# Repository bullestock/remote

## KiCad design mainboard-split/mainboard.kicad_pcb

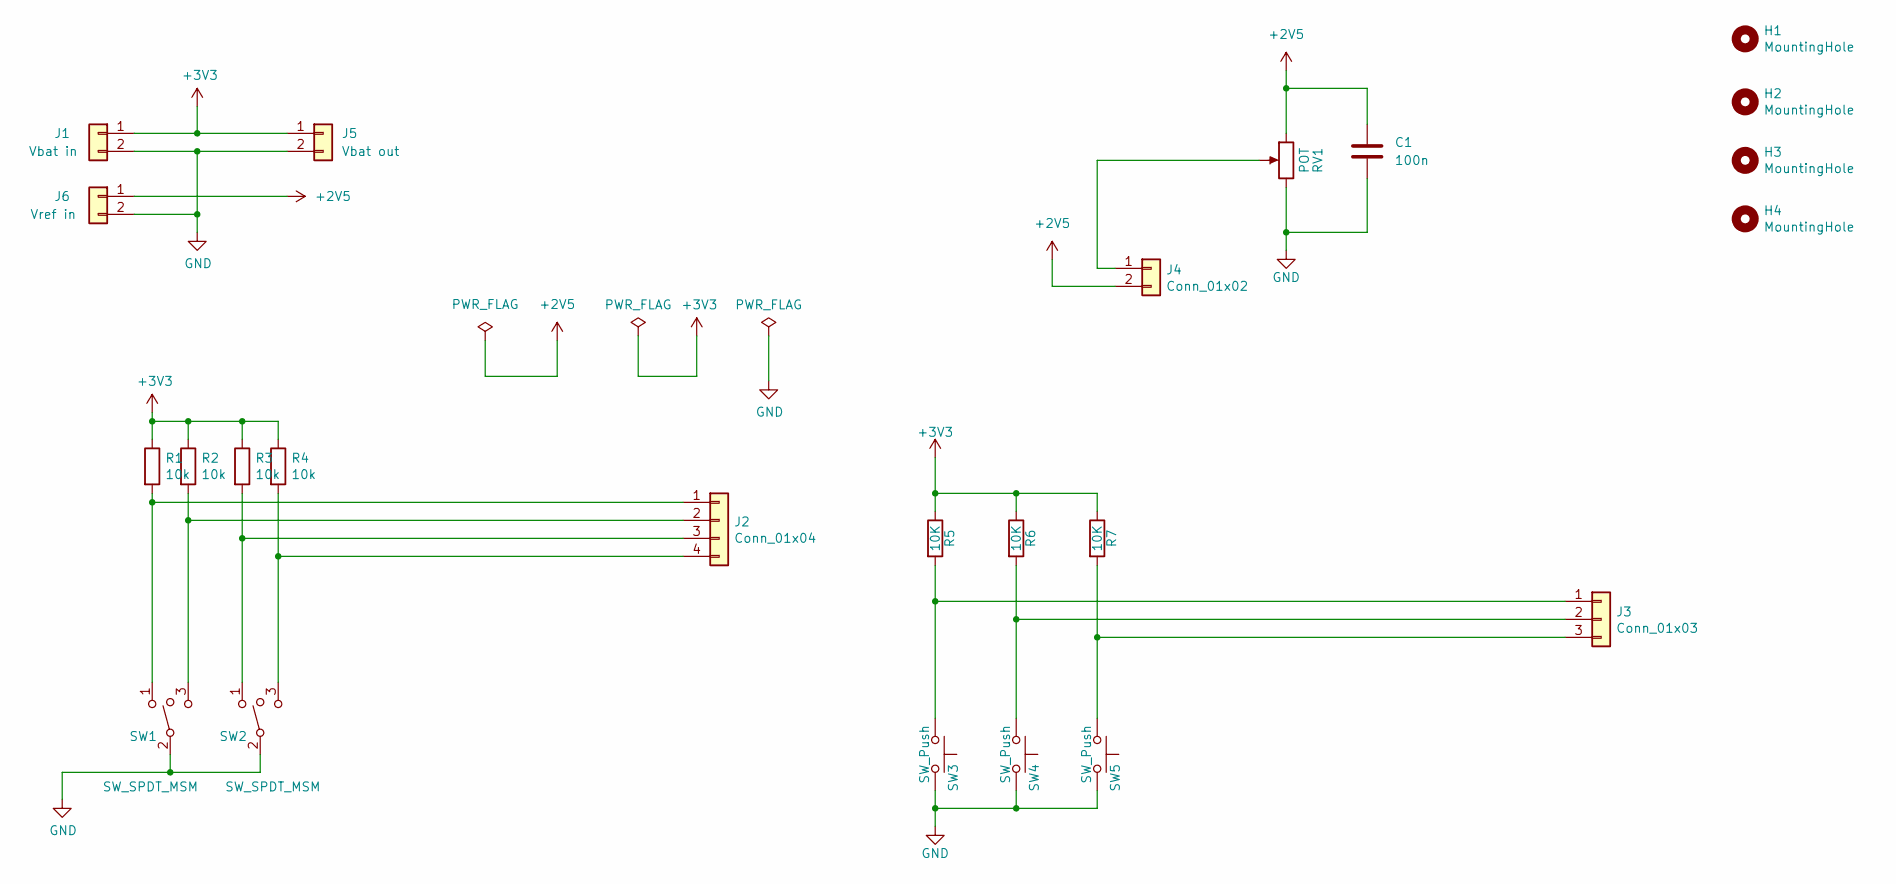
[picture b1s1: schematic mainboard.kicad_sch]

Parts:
C1: 100n; C_0603_1608Metric
H1, H2, H3, H4: MountingHole; MountingHole_3.2mm_M3
J1: Vbat in; JST_XH_B02B-XH-A_1x02_P2.50mm_Vertical
J2: Conn_01x04; JST_XH_B04B-XH-A_1x04_P2.50mm_Vertical
J3: Conn_01x03; JST_XH_B03B-XH-A_1x03_P2.50mm_Vertical
J4: Conn_01x02; JST_XH_B02B-XH-A_1x02_P2.50mm_Vertical
J5: Vbat out; JST_XH_B02B-XH-A_1x02_P2.50mm_Vertical
J6: Vref in; JST_XH_B02B-XH-A_1x02_P2.50mm_Vertical
R1, R2, R3, R4: 10k; R_0603_1608Metric
R5, R6, R7: 10K; R_0603_1608Metric
RV1: POT; Potentiometer_6mm_axis_square
SW1, SW2: SW_SPDT_MSM; Switch_1x03_P5.08mm
SW3, SW4, SW5: SW_Push; Switch_1x02_P6mm

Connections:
+2V5: C1.1, J4.2, J6.1, RV1.1
+3V3: J1.1, J5.1, R1.1, R2.1, R3.1, R4.1, R5.1, R6.1, R7.1
GND: C1.2, J1.2, J5.2, J6.2, RV1.3, SW1.2, SW2.2, SW3.2, SW4.2, SW5.2
unnamed: J2.1, R1.2, SW1.1
unnamed: J2.2, R2.2, SW1.3
unnamed: J2.3, R3.2, SW2.1
unnamed: J2.4, R4.2, SW2.3
unnamed: J3.1, R5.2, SW3.1
unnamed: J3.2, R6.2, SW4.1
unnamed: J3.3, R7.2, SW5.1
unnamed: J4.1, RV1.2

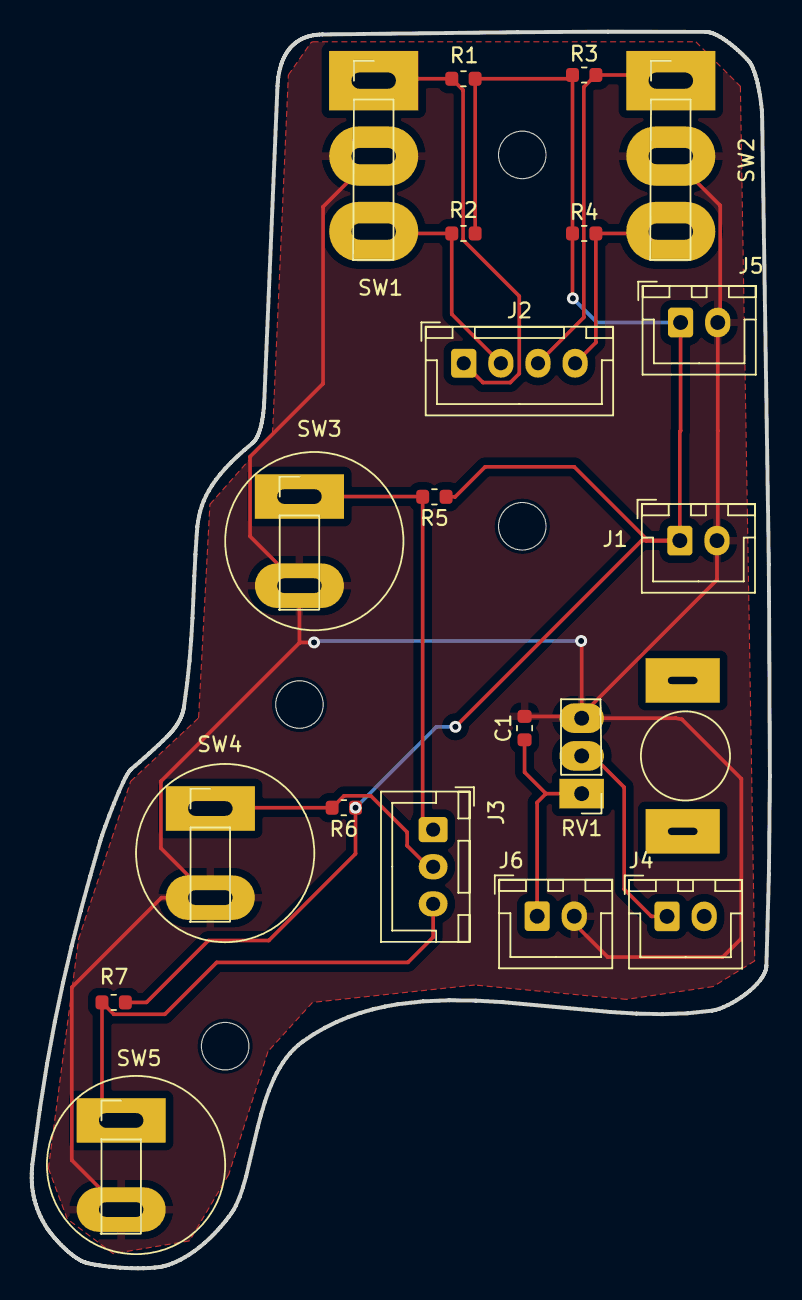
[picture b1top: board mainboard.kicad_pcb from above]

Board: 2 copper layers, 49.7 x 83.3 mm, 24 parts (0 on the bottom side), 11 nets.

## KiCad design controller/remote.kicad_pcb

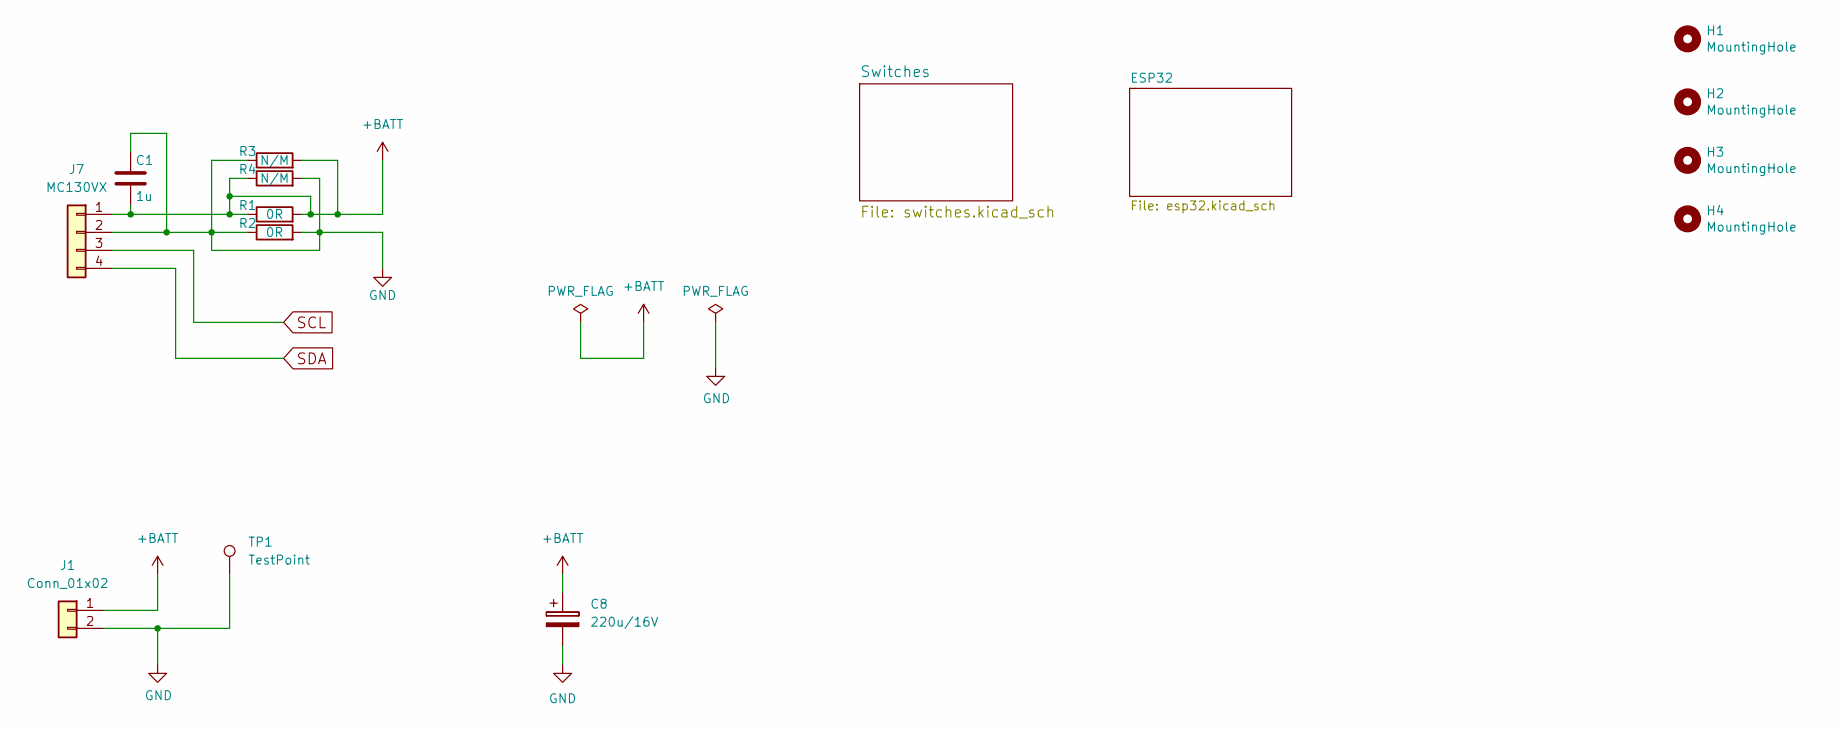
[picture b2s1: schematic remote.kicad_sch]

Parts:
C1: 1u; C_0603_1608Metric
C8: 220u/16V; CP_Elec_10x10.5
H1, H2, H3, H4: MountingHole; MountingHole_3.2mm_M3
J1: Conn_01x02; JST_XH_B02B-XH-A_1x02_P2.50mm_Vertical
J7: MC130VX; PinSocket_1x04_P2.54mm_Vertical
R1, R2: 0R; R_0603_1608Metric
R3, R4: N/M; R_0603_1608Metric
TP1: TestPoint; TestPoint_Keystone_5000-5004_Miniature

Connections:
+BATT: C1.2, C8.1, J1.1, J7.1, R1.1, R1.2, R3.2, R4.1; also elsewhere on the board
GND: C1.1, C8.2, J1.2, J7.2, R2.1, R2.2, R3.1, R4.2, TP1.1; also elsewhere on the board
SCL: J7.3; also elsewhere on the board
SDA: J7.4; also elsewhere on the board

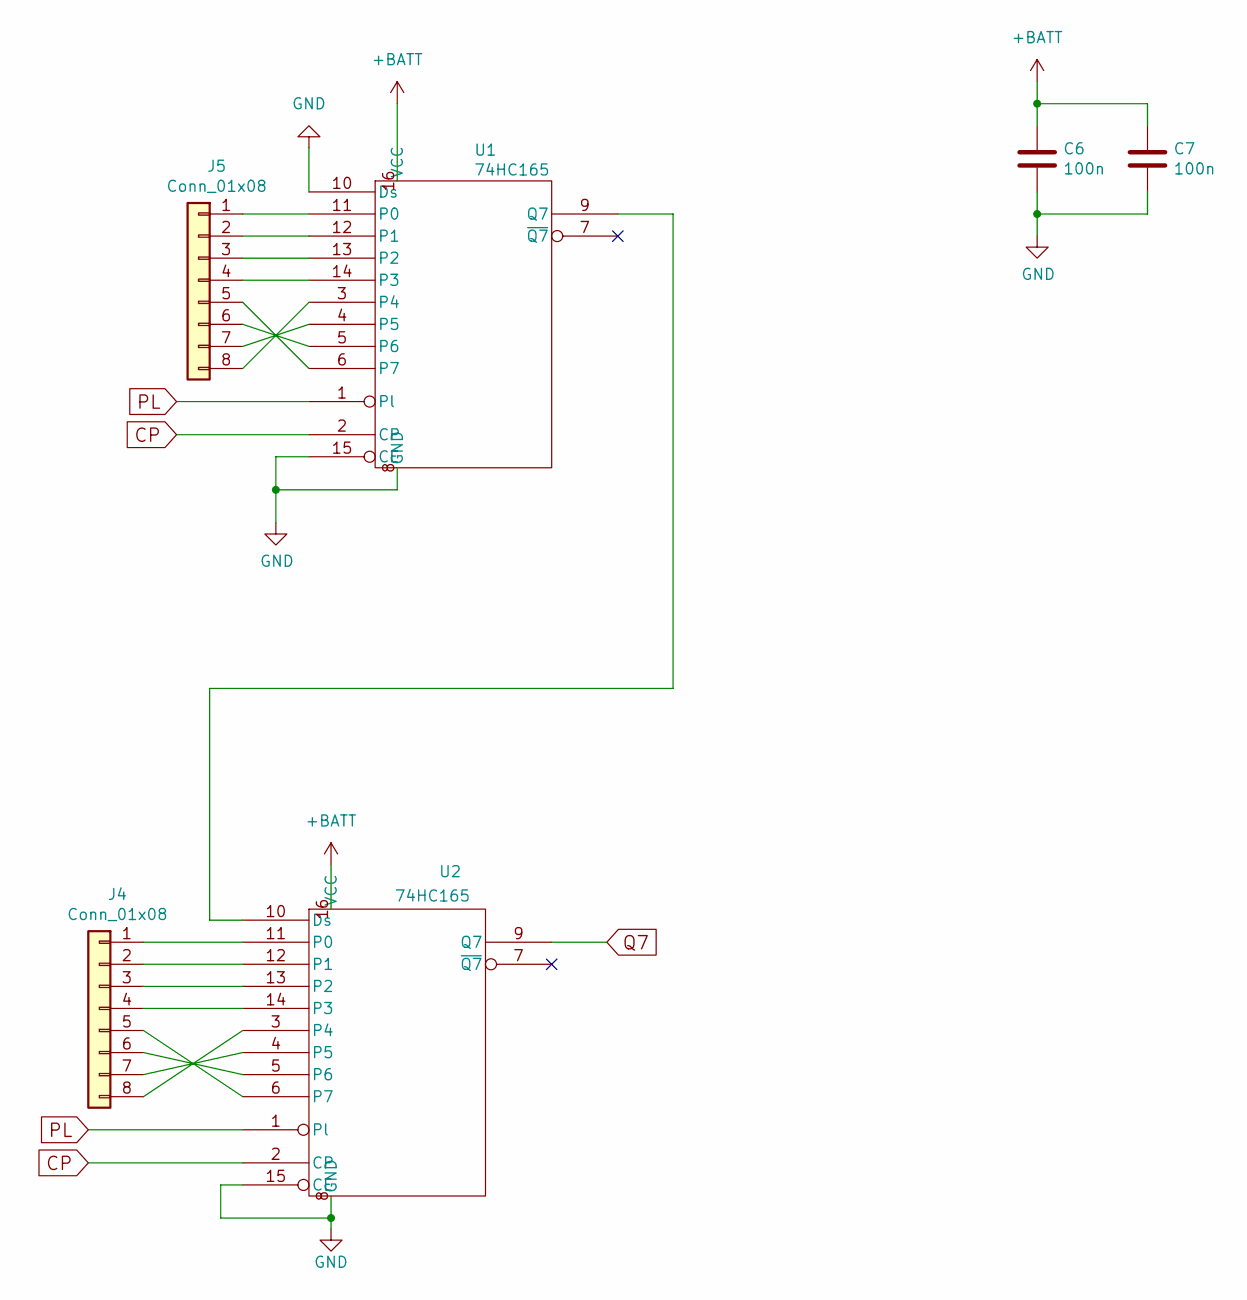
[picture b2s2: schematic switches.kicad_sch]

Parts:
C6, C7: 100n; C_0603_1608Metric
J4, J5: Conn_01x08; JST_XH_B08B-XH-A_1x08_P2.50mm_Vertical
U1, U2: 74HC165; SOP-16_3.9x9.9mm_P1.27mm

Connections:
+BATT: C6.1, C7.1, U1.16 (VCC), U2.16 (VCC); also elsewhere on the board
CP: U1.2 (CP), U2.2 (CP); also elsewhere on the board
GND: C6.2, C7.2, U1.8 (GND), U1.10 (Ds), U1.15 (CE), U2.8 (GND), U2.15 (CE); also elsewhere on the board
unnamed: J4.1, U2.11 (P0)
unnamed: J4.2, U2.12 (P1)
unnamed: J4.3, U2.13 (P2)
unnamed: J4.4, U2.14 (P3)
unnamed: J4.5, U2.6 (P7)
unnamed: J4.6, U2.5 (P6)
unnamed: J4.7, U2.4 (P5)
unnamed: J4.8, U2.3 (P4)
unnamed: J5.1, U1.11 (P0)
unnamed: J5.2, U1.12 (P1)
unnamed: J5.3, U1.13 (P2)
unnamed: J5.4, U1.14 (P3)
unnamed: J5.5, U1.6 (P7)
unnamed: J5.6, U1.5 (P6)
unnamed: J5.7, U1.4 (P5)
unnamed: J5.8, U1.3 (P4)
unnamed: U1.9 (Q7), U2.10 (Ds)
PL: U1.1 (Pl), U2.1 (Pl); also elsewhere on the board
Q7: U2.9 (Q7); also elsewhere on the board

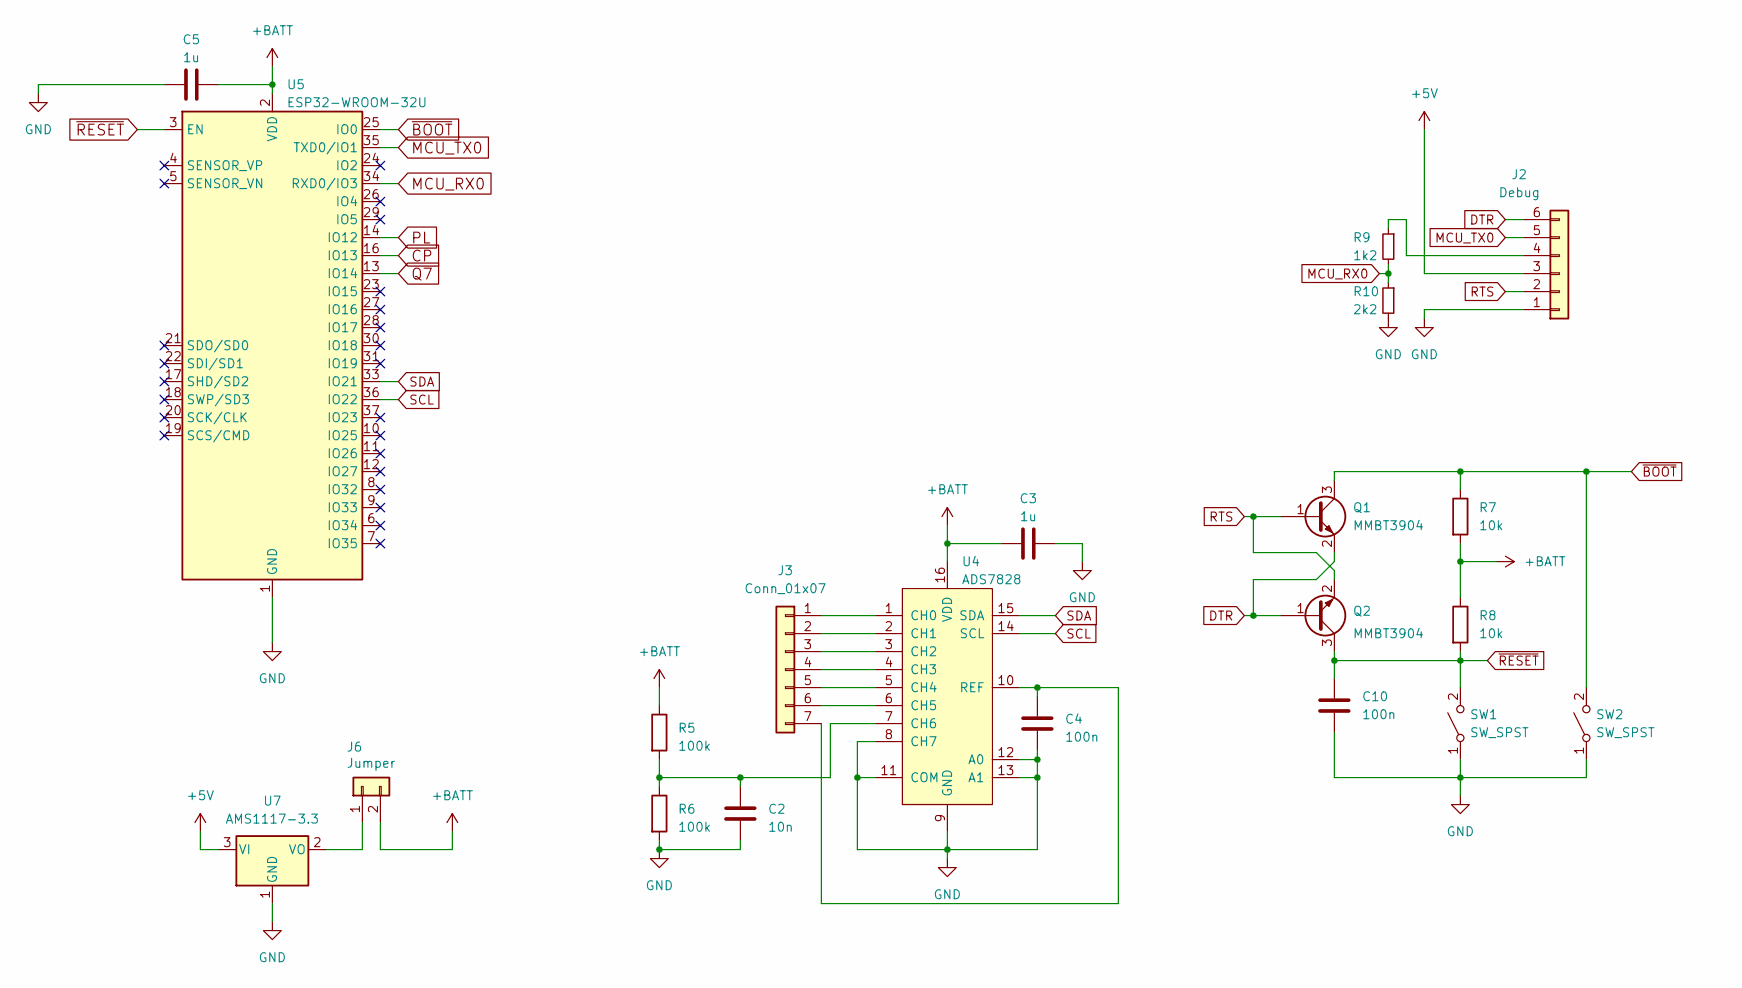
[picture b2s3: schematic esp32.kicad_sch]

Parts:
C2: 10n; C_0603_1608Metric
C3, C5: 1u; C_0603_1608Metric
C4, C10: 100n; C_0603_1608Metric
J2: Debug; PinHeader_1x06_P2.54mm_Vertical
J3: Conn_01x07; JST_XH_B07B-XH-A_1x07_P2.50mm_Vertical
J6: Jumper; PinHeader_1x02_P2.54mm_Vertical
Q1, Q2: MMBT3904; SOT-23
R5, R6: 100k; R_0603_1608Metric
R7, R8: 10k; R_0603_1608Metric
R9: 1k2; R_0603_1608Metric
R10: 2k2; R_0603_1608Metric
SW1, SW2: SW_SPST; SW_SPST_CK_RS282G05A3
U4: ADS7828; TSSOP-16_4.4x5mm_P0.65mm
U5: ESP32-WROOM-32U
U7: AMS1117-3.3; SOT-223-3_TabPin2

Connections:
+5V: J2.3, U7.3 (VI)
+BATT: C3.1, C5.2, J6.2, R5.1, R7.2, R8.1, U4.16 (VDD), U5.2 (VDD); also elsewhere on the board
CP: U5.16 (IO13); also elsewhere on the board
DTR: J2.6, Q1.2 (E), Q2.1 (B)
GND: C2.2, C3.2, C4.2, C5.1, C10.2, J2.1, R6.2, R10.2, SW1.1 (A), SW2.1 (A), U4.8 (CH7), U4.9 (GND), U4.11 (COM), U4.12 (A0), U4.13 (A1), U5.1 (GND), U5.15 (GND), U5.38 (GND), U5.39 (GND), U7.1 (GND); also elsewhere on the board
MCU_RX0: R9.2, R10.1, U5.34 (RXD0/IO3)
MCU_TX0: J2.5, U5.35 (TXD0/IO1)
unnamed: J2.4, R9.1
unnamed: J3.1, U4.1 (CH0)
unnamed: J3.2, U4.2 (CH1)
unnamed: J3.3, U4.3 (CH2)
unnamed: J3.4, U4.4 (CH3)
unnamed: J3.5, U4.5 (CH4)
unnamed: J3.6, U4.6 (CH5)
unnamed: C4.1, J3.7, U4.10 (REF)
unnamed: J6.1, U7.2 (VO)
unnamed: C2.1, R5.2, R6.1, U4.7 (CH6)
PL: U5.14 (IO12); also elsewhere on the board
Q7: U5.13 (IO14); also elsewhere on the board
RTS: J2.2, Q1.1 (B), Q2.2 (E)
SCL: U4.14 (SCL), U5.36 (IO22); also elsewhere on the board
SDA: U4.15 (SDA), U5.33 (IO21); also elsewhere on the board
~BOOT: Q1.3 (C), R7.1, SW2.2 (B), U5.25 (IO0)
~RESET: C10.1, Q2.3 (C), R8.2, SW1.2 (B), U5.3 (EN)

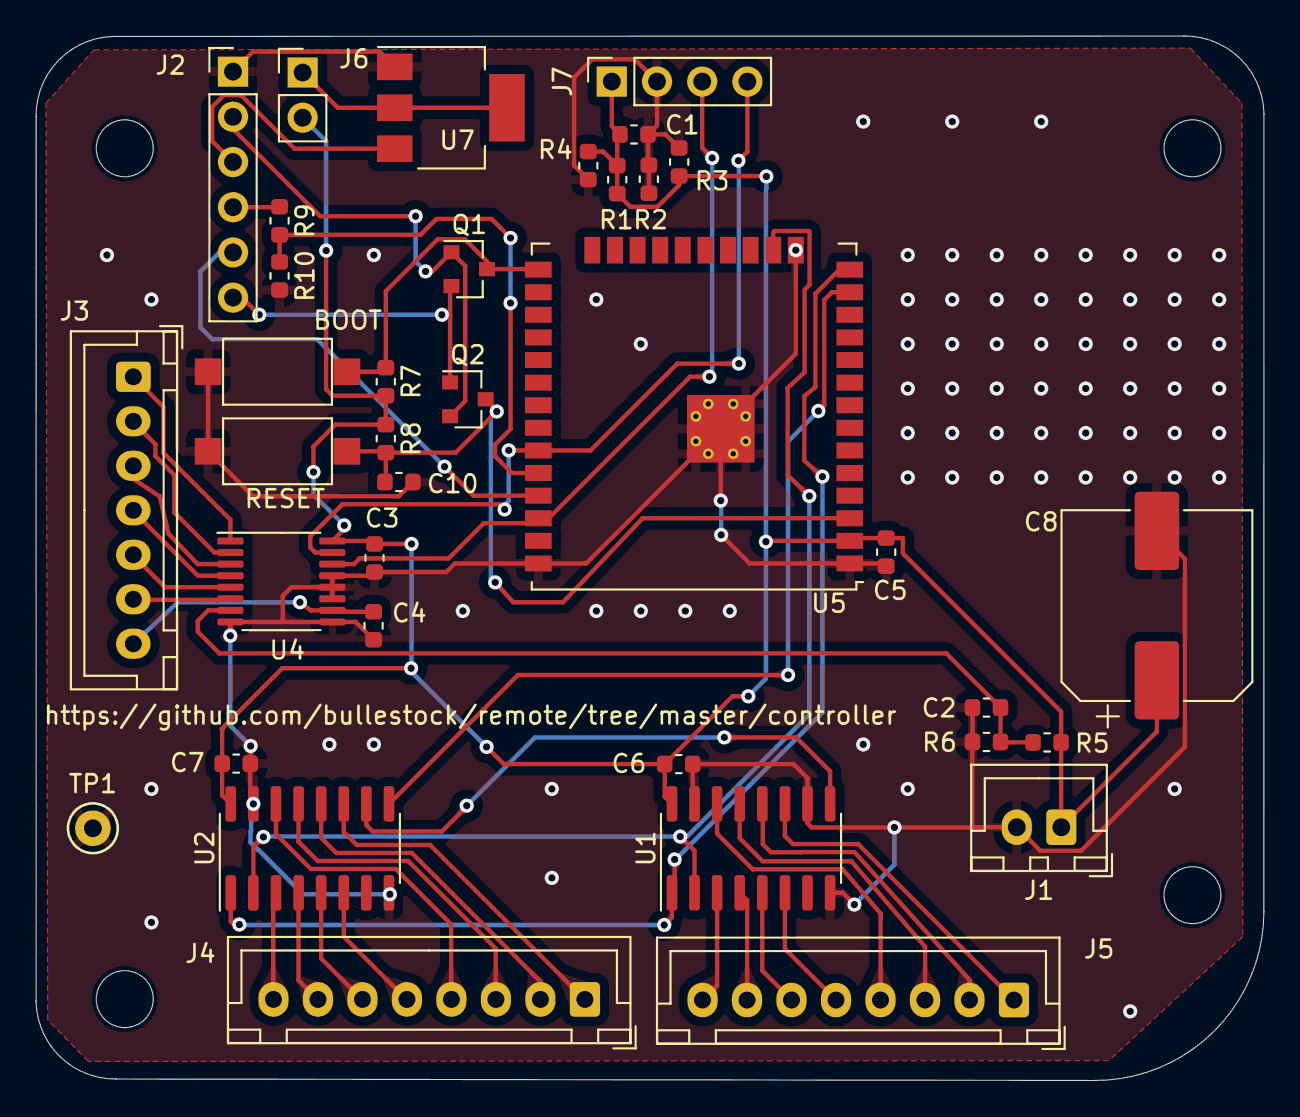
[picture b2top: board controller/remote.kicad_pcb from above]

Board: 2 copper layers, 69.0 x 58.7 mm, 40 parts (0 on the bottom side), 41 nets.

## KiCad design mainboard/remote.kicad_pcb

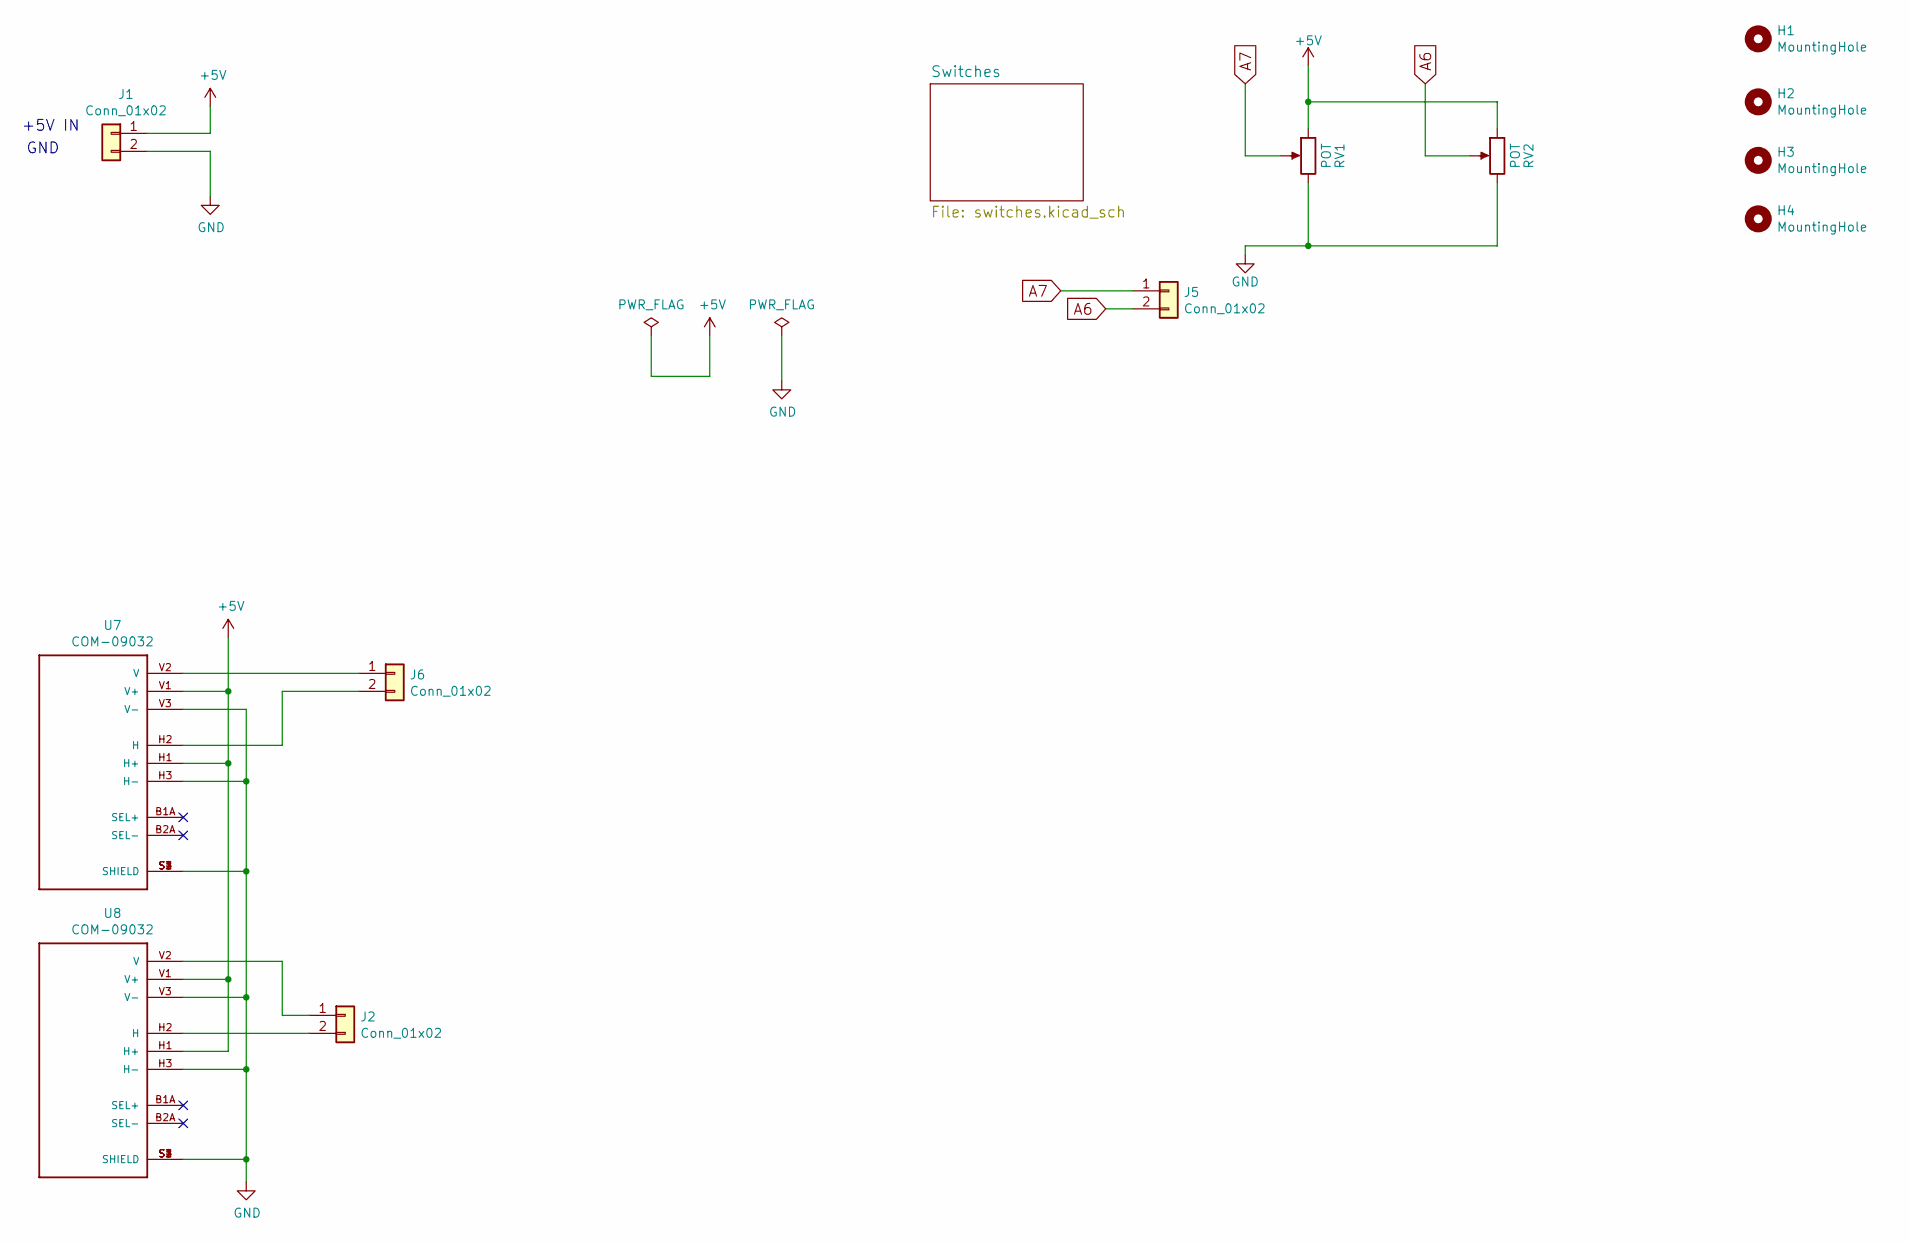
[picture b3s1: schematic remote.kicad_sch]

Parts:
H1, H2, H3, H4: MountingHole; MountingHole_3.2mm_M3
J1, J2, J5, J6: Conn_01x02; JST_XH_B02B-XH-A_1x02_P2.50mm_Vertical_Milling
RV1, RV2: POT; Potentiometer_6mm_axis_square
U7, U8: COM-09032; AnalogJoystick_ALPS_10k

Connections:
+5V: J1.1, RV1.1, RV2.1, U7.H1 (H+), U7.V1 (V+), U8.H1 (H+), U8.V1 (V+); also elsewhere on the board
A6: J5.2, RV2.2
A7: J5.1, RV1.2
GND: J1.2, RV1.3, RV2.3, U7.H3 (H-), U7.S1 (SHIELD), U7.S2 (SHIELD), U7.S3 (SHIELD), U7.S4 (SHIELD), U7.V3 (V-), U8.H3 (H-), U8.S1 (SHIELD), U8.S2 (SHIELD), U8.S3 (SHIELD), U8.S4 (SHIELD), U8.V3 (V-); also elsewhere on the board
unnamed: J2.1, U8.V2 (V)
unnamed: J2.2, U8.H2 (H)
unnamed: J6.1, U7.V2 (V)
unnamed: J6.2, U7.H2 (H)

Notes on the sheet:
GND
+5V IN

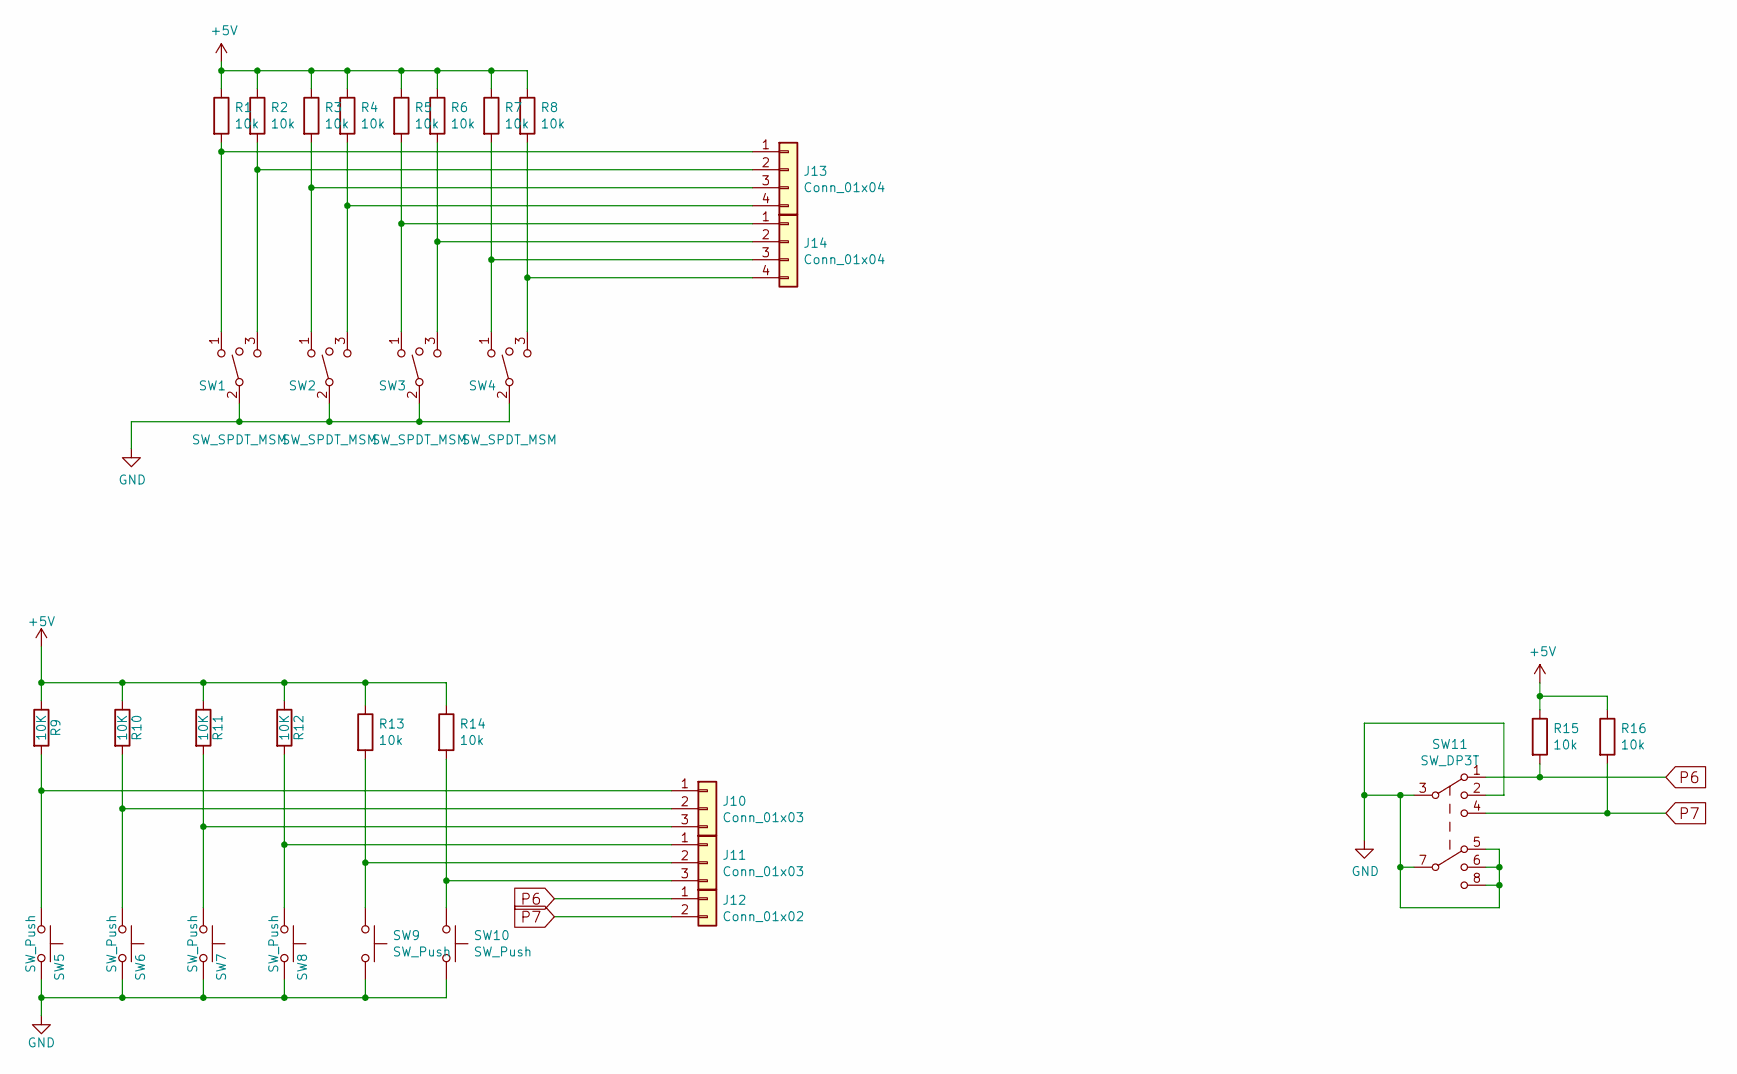
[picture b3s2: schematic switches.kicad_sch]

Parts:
J10, J11: Conn_01x03; JST_XH_B03B-XH-A_1x03_P2.50mm_Vertical_Milling
J12: Conn_01x02; JST_XH_B02B-XH-A_1x02_P2.50mm_Vertical_Milling
J13, J14: Conn_01x04; JST_XH_B04B-XH-A_1x04_P2.50mm_Vertical_Milling
R1, R2, R3, R4, R5, R6, R7, R8, R13, R14, R15, R16: 10k; R_0805_2012Metric
R9, R10, R11, R12: 10K; R_0805_2012Metric
SW1, SW2, SW3, SW4: SW_SPDT_MSM; Switch_1x03_P5.08mm
SW5, SW6, SW7, SW8, SW9, SW10: SW_Push; Switch_1x02_P6mm
SW11: SW_DP3T; Switch_2x03_P3mm_Slide

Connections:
+5V: R1.1, R2.1, R3.1, R4.1, R5.1, R6.1, R7.1, R8.1, R9.1, R10.1, R11.1, R12.1, R13.1, R14.1, R15.1, R16.1; also elsewhere on the board
GND: SW1.2, SW2.2, SW3.2, SW4.2, SW5.2, SW6.2, SW7.2, SW8.2, SW9.2, SW10.2, SW11.2, SW11.3, SW11.5, SW11.6, SW11.7, SW11.8; also elsewhere on the board
unnamed: J10.1, R9.2, SW5.1
unnamed: J10.2, R10.2, SW6.1
unnamed: J10.3, R11.2, SW7.1
unnamed: J11.1, R12.2, SW8.1
unnamed: J11.2, R13.2, SW9.1
unnamed: J11.3, R14.2, SW10.1
unnamed: J13.1, R1.2, SW1.1
unnamed: J13.2, R2.2, SW1.3
unnamed: J13.3, R3.2, SW2.1
unnamed: J13.4, R4.2, SW2.3
unnamed: J14.1, R5.2, SW3.1
unnamed: J14.2, R6.2, SW3.3
unnamed: J14.3, R7.2, SW4.1
unnamed: J14.4, R8.2, SW4.3
P6: J12.1, R15.2, SW11.1
P7: J12.2, R16.2, SW11.4

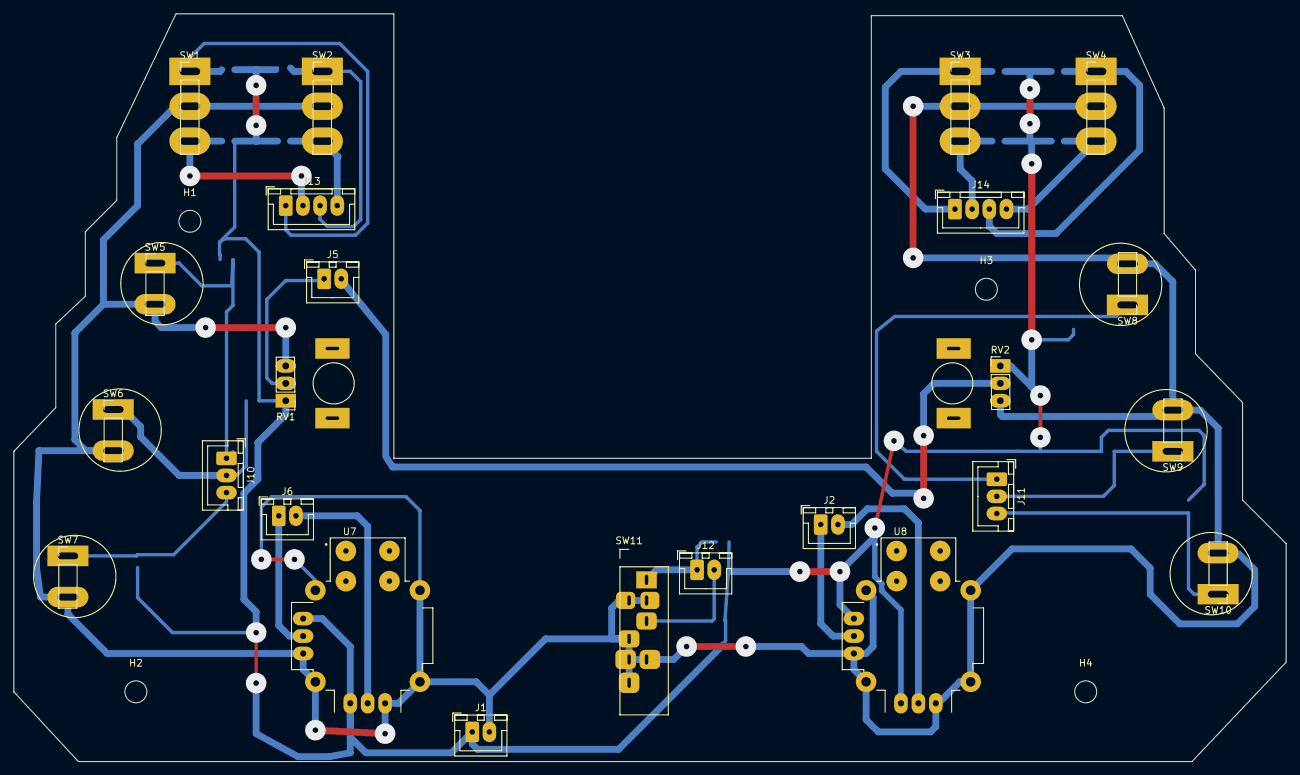
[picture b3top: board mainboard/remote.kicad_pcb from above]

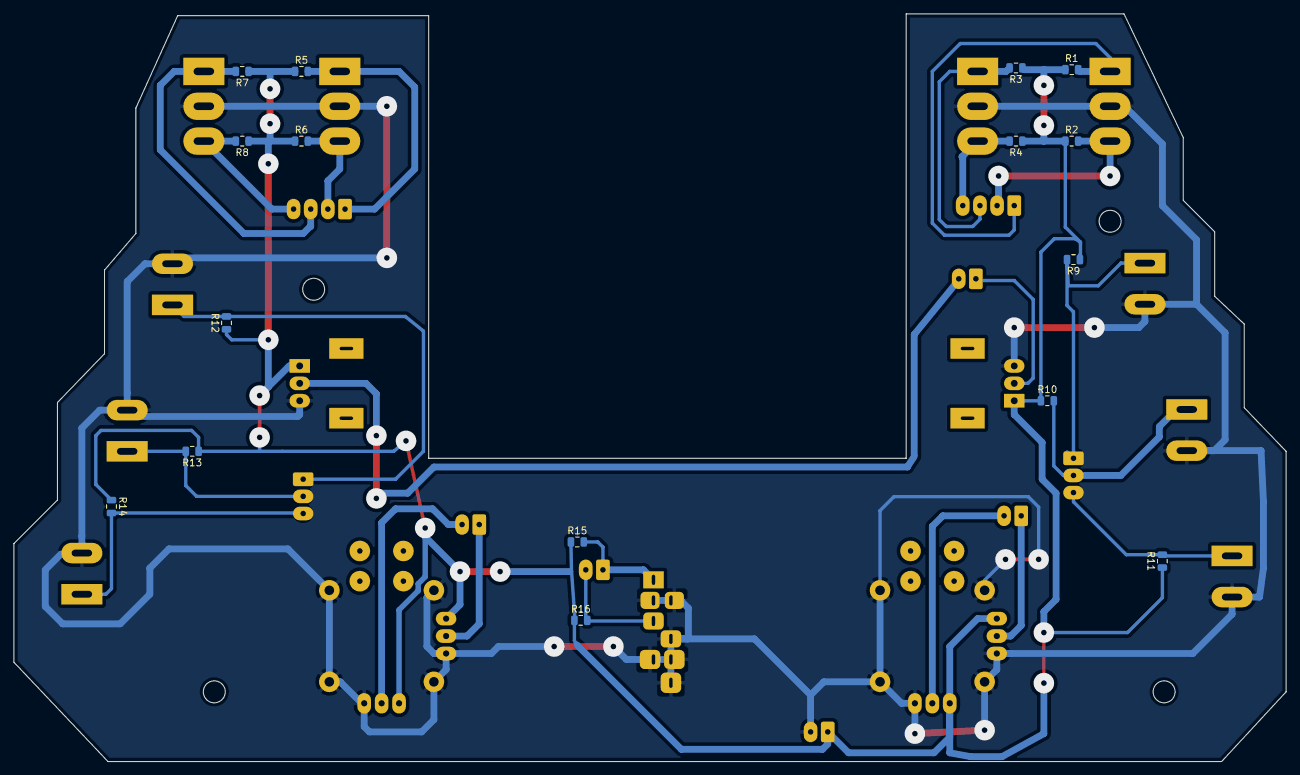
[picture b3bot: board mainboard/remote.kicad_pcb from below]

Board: 2 copper layers, 185.4 x 109.0 mm, 44 parts (16 on the bottom side), 24 nets.

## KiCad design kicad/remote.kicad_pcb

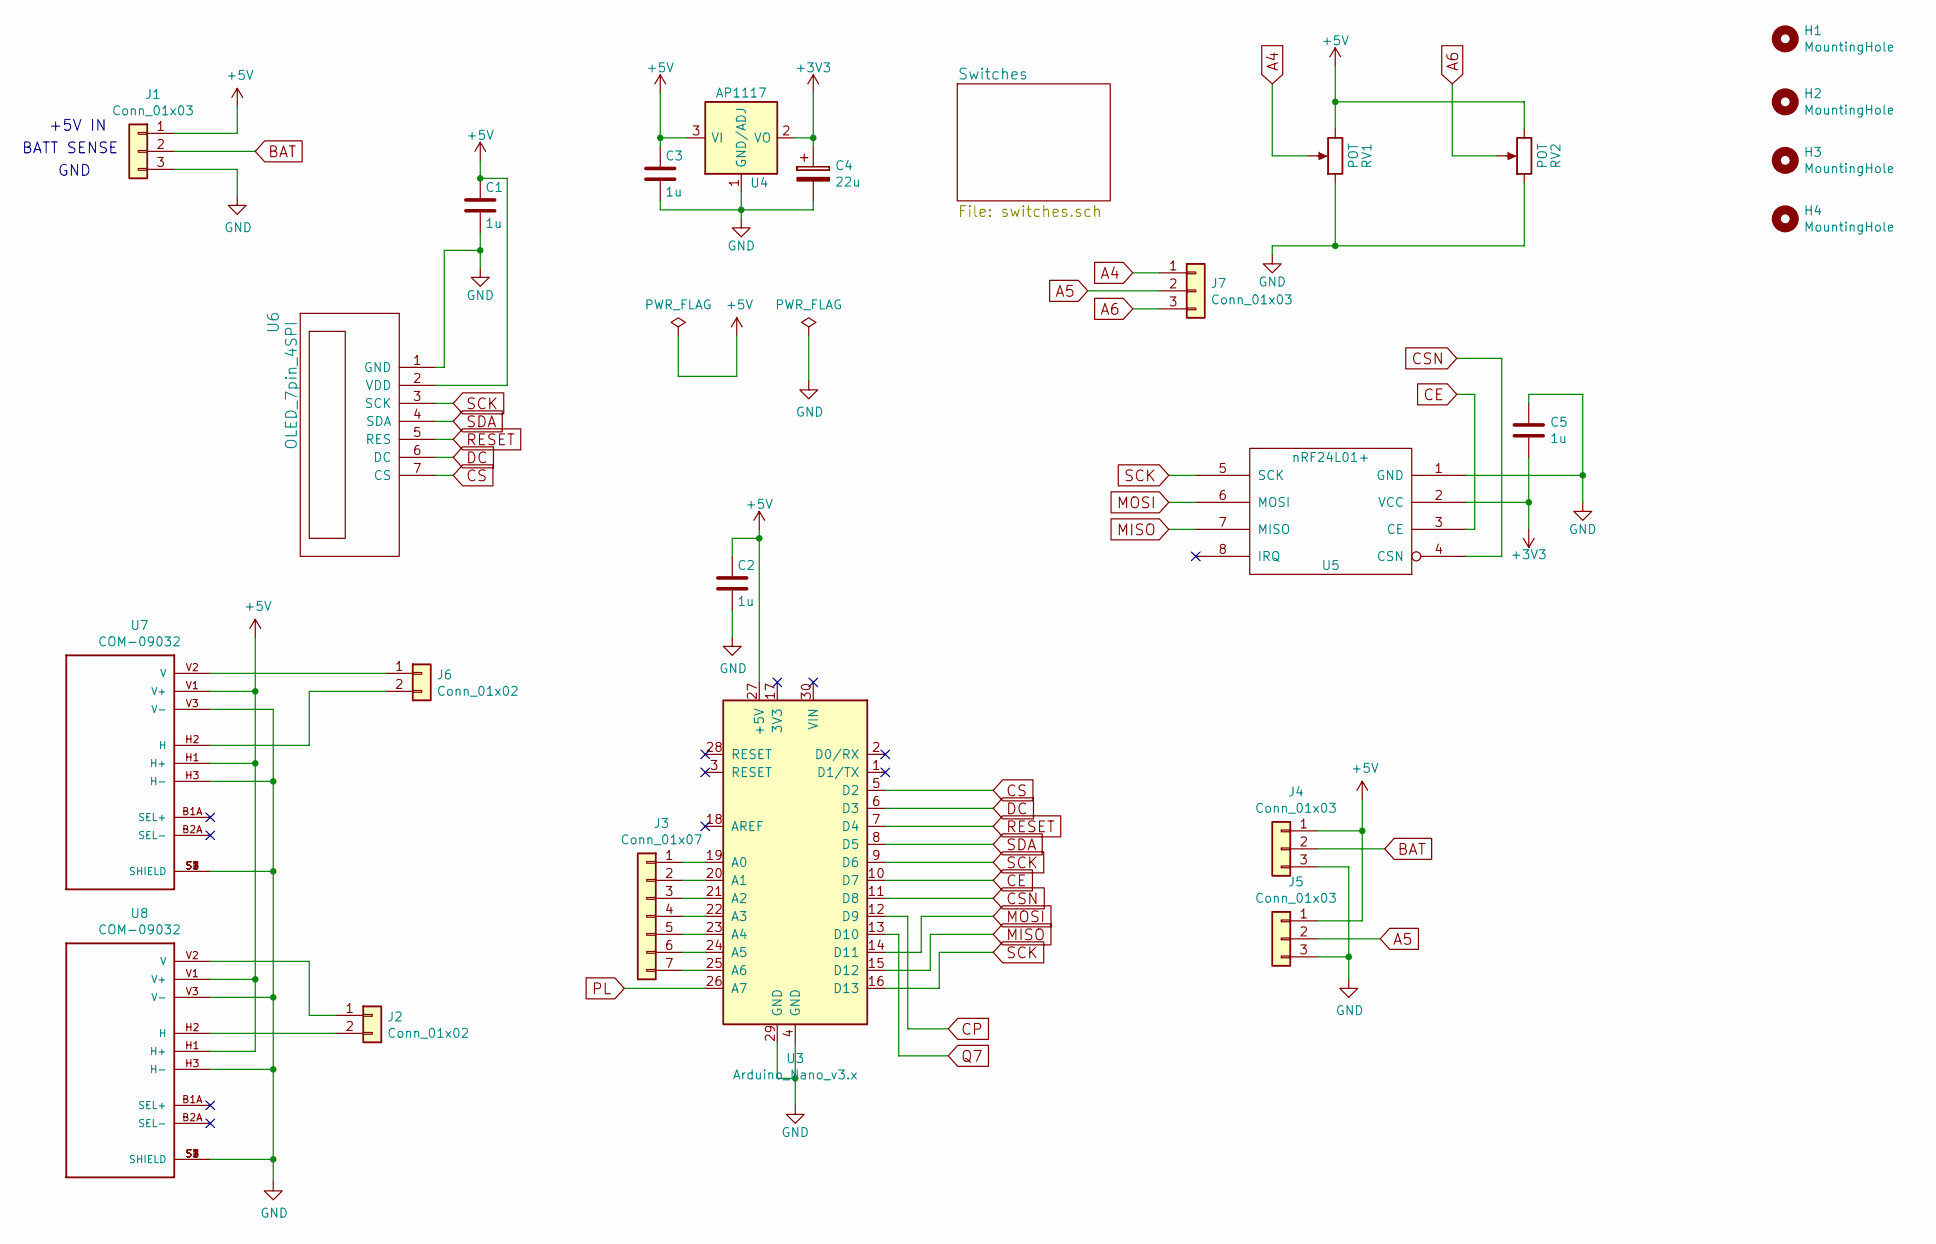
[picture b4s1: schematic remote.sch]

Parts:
C1, C2, C3, C5: 1u; C_0805_2012Metric
C4: 22u; C_1206_3216Metric
H1, H2, H3, H4: MountingHole; MountingHole_3.2mm_M3
J1, J4, J5, J7: Conn_01x03; JST_XH_B03B-XH-A_1x03_P2.50mm_Vertical_Milling
J2, J6: Conn_01x02; JST_XH_B02B-XH-A_1x02_P2.50mm_Vertical_Milling
J3: Conn_01x07; JST_XH_B07B-XH-A_1x07_P2.50mm_Vertical
RV1, RV2: POT; Potentiometer_4mm_axis
U3: Arduino_Nano_v3.x; Arduino_Nano
U4: AP1117; SOT-223
U5: nRF24L01+; nRF24L01
U6: OLED_7pin_4SPI; Display_OLED_7pin_4SPI
U7, U8: COM-09032; XDCR_COM-09032

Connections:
+3V3: C4.1, C5.2, U4.2 (VO), U4.4 (VO), U5.2 (VCC)
+5V: C1.1, C2.1, C3.1, J1.1, J4.1, J5.1, RV1.3, RV2.3, U3.27 (+5V), U4.3 (VI), U6.2 (VDD), U7.H1 (H+), U7.V1 (V+), U8.H1 (H+), U8.V1 (V+); also elsewhere on the board
A4: J7.1, RV1.2
A5: J5.2, J7.2
A6: J7.3, RV2.2
BAT: J1.2, J4.2
CE: U3.10 (D7), U5.3 (CE)
CP: U3.12 (D9); also elsewhere on the board
CS: U3.5 (D2), U6.7 (CS)
CSN: U3.11 (D8), U5.4 (CSN)
DC: U3.6 (D3), U6.6 (DC)
GND: C1.2, C2.2, C3.2, C4.2, C5.1, J1.3, J4.3, J5.3, RV1.1, RV2.1, U3.4 (GND), U3.29 (GND), U4.1 (GND/ADJ), U5.1 (GND), U6.1 (GND), U7.H3 (H-), U7.S1 (SHIELD), U7.S2 (SHIELD), U7.S3 (SHIELD), U7.S4 (SHIELD), U7.V3 (V-), U8.H3 (H-), U8.S1 (SHIELD), U8.S2 (SHIELD), U8.S3 (SHIELD), U8.S4 (SHIELD), U8.V3 (V-); also elsewhere on the board
MISO: U3.15 (D12), U5.7 (MISO)
MOSI: U3.14 (D11), U5.6 (MOSI)
unnamed: J2.1, U8.V2 (V)
unnamed: J2.2, U8.H2 (H)
unnamed: J3.1, U3.19 (A0)
unnamed: J3.2, U3.20 (A1)
unnamed: J3.3, U3.21 (A2)
unnamed: J3.4, U3.22 (A3)
unnamed: J3.5, U3.23 (A4)
unnamed: J3.6, U3.24 (A5)
unnamed: J3.7, U3.25 (A6)
unnamed: J6.1, U7.V2 (V)
unnamed: J6.2, U7.H2 (H)
PL: U3.26 (A7); also elsewhere on the board
Q7: U3.13 (D10); also elsewhere on the board
RESET: U3.7 (D4), U6.5 (RES)
SCK: U3.9 (D6), U3.16 (D13), U5.5 (SCK), U6.3 (SCK)
SDA: U3.8 (D5), U6.4 (SDA)

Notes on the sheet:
+5V IN
GND
BATT SENSE
